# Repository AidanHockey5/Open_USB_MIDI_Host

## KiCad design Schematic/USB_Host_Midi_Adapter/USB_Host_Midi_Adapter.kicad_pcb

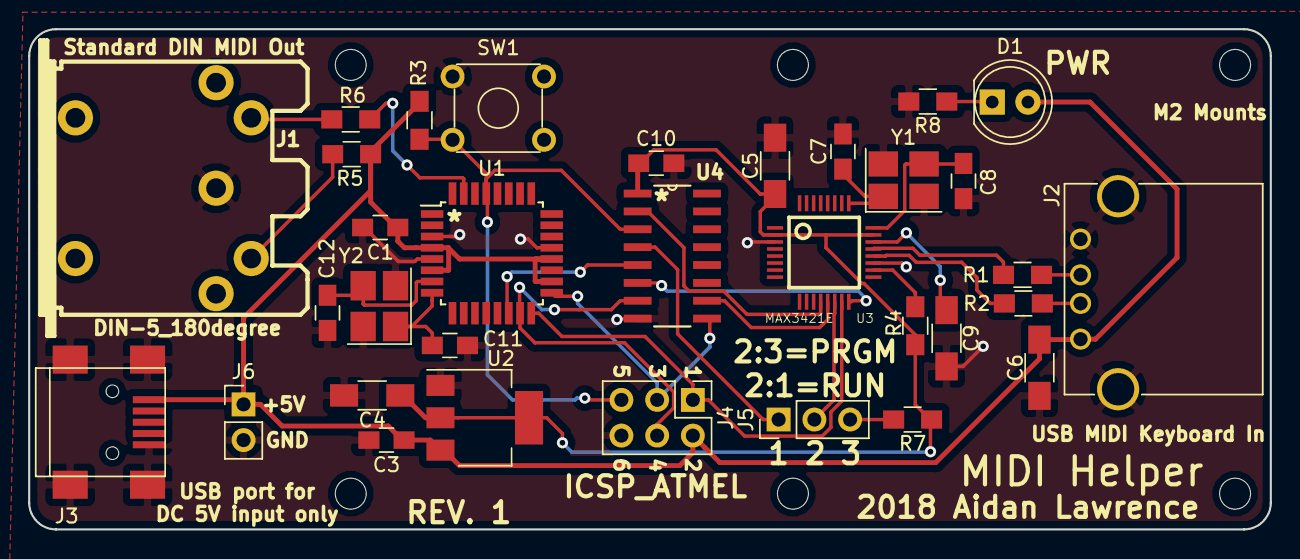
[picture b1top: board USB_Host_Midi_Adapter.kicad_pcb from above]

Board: 2 copper layers, 88.3 x 35.6 mm, 39 parts (0 on the bottom side), 28 nets.

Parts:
C1, C3, C10: 100nF; C_0805_HandSoldering
C4: 10uF; C_1206_HandSoldering
C5, C9: 1uF; C_1206_HandSoldering
C6: 4.7uF; C_1206_HandSoldering
C7, C8, C11, C12: 20pF; C_0805_HandSoldering
D1: LED; LED_D5.0mm
J1: DIN-5_180degree; din-5
J2: USB_A
J3: USB_OTG; USB_Mini-B
J4: ICSP_ATMEL; Pin_Header_Straight_2x03_Pitch2.54mm
J5: PROG_JMPR; Pin_Header_Straight_1x03_Pitch2.54mm
J6: PWR_IN; Pin_Header_Straight_1x02_Pitch2.54mm
MNT1, MNT2, MNT3, MNT3#2, MNT3#3, MNT4: MountingHole_2.2mm_M2
R1, R2: 33; R_0805_HandSoldering
R3, R7: 10K; R_0805_HandSoldering
R4: 2.2K; R_0805_HandSoldering
R5, R6, R8: 220; R_0805_HandSoldering
SW1: SW_RESET; SW_TH_Tactile_Omron_B3F-10xx
U1: ATMEGA328P-AU; TQFP-32_7x7mm_Pitch0.8mm
U2: LD1117S33TR_SOT223; SOT-223-3_TabPin2
U3: MAX3421E; TQFP32-5MM
U4: MM74HC4050M; SOIC127P600X175-16N
Y1: 12MHz; Crystal_SMD_3225-4pin_3.2x2.5mm_HandSoldering
Y2: 16MHz; Crystal_SMD_3225-4pin_3.2x2.5mm_HandSoldering

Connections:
+3V3: C4.1, C5.1, C10.1, R4.2, R7.1, U2.2, U3.2, U3.23, U4.1
+5V: C1.1, C3.1, C6.2, D1.2, J2.1, J3.1, J4.2, J6.1, R3.1, R5.2, U1.4, U1.6, U1.18, U1.20, U2.3
CS: U1.14, U4.5
D+: R1.1, U3.21
D-: R2.1, U3.20
GND: C1.2, C3.2, C4.2, C5.2, C6.1, C7.1, C8.1, C9.2, C10.2, C11.1, C12.1, J1.2, J2.4, J2.5, J3.5, J3.6, J4.6, J6.2, R8.2, SW1.1, U1.3, U1.5, U1.21, U2.1, U3.3, U3.19, U4.8, Y1.2, Y1.4, Y2.2, Y2.4
MISO: J4.1, U1.16, U3.15
MOSI: J4.4, U1.15, U4.7
unnamed: C7.2, U3.25, Y1.1
unnamed: C8.2, U3.24, Y1.3
unnamed: C9.1, U3.22
unnamed: C11.2, U1.8, Y2.1
unnamed: C12.2, U1.7, Y2.3
unnamed: D1.1, R8.1
unnamed: J1.4, R5.1
unnamed: J1.5, R6.2
unnamed: J2.2, R2.2
unnamed: J2.3, R1.2
unnamed: J5.3, R7.2
unnamed: R4.1, U3.18
RESET: J4.5, R3.2, SW1.3, U1.29, U4.3
SCK: J4.3, U1.17, U4.9
TX: R6.1, U1.31
_cs: J5.2, U3.14
_cs_prejmp: J5.1, U4.4
_mosi: U3.16, U4.6
_reset: U3.12, U4.2
_sck: U3.13, U4.10

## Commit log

2018-10-21 Schematic complete. Begin PCB layout
2018-10-21 PCB Done.
2018-10-21 Board complete, dispatch for manufacture
